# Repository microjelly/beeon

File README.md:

# beeon

## Overview
The classic device was created several years ago to fill a single need, preventing my work computer from auto locking due to inactivity. *Subverting security policy comes with a responsibility to ensure that you lock your computer (CTRL+ALT+DEL) everytime you walk away!*  

## classic notes
### flash bootloader to board
`avrdude -c USBasp -p attiny85 -U flash:w:beeon-classic-v1-micronucleus-2.04.hex:i -B 10`  
`avrdude -c USBasp -p attiny85 -U lfuse:w:0xe1:m -U hfuse:w:0xdd:m -U efuse:w:0xfe:m`  
### upload new firmware onto board
`micronucleus --run {firmware.hex}`
### clear out any existing firmware
`micronucleus --erase-only`
### upload firmware with random serial number
*first create random serial number file*  
`beeon-classic-sn -mk -mk-p=Z-ZZ > beeon-sn.txt`  
`beeon-classic-sn | micronucleus --run -`

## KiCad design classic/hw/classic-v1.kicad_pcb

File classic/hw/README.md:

[finished-product-image]: v1/img/classic-v1.jpg "BEEON - Classic; v1"
[pcb-top-image]: v1/img/classic-v1-top.png "BEEON - Classic; v1; pcb-top"
[pcb-bottom-image]: v1/img/classic-v1-bottom.png "BEEON - Classic; v1; pcb-bottom"

# classic hardware

## Overview
A brief overview of why we ave a classic version

## BOM
Some words aboutthe current bom
| Reference(s) | Package  | Description                    | Manufacturer      | Part Number        | Cost  |
| ------------ | -------: | ------------------------------ | ----------------- | -----------------: | ----: |
| SW1          |          | Switch                         | E-Switch          | *TL1014BF180QG     | $#.## |
| D1           | 1206     | LED                            | OSRAM Opto        | *LG N971-KN-1      | $#.## |
| J1           |          | 6 PIN 2.54mm (Optional Header) | Harwin            | M20-7820646        | $0.95 |
| J2           |          | USB                            | CNC-Tech          | 1001-011-01101     | $0.77 |
| R1           | 0805     | 47 Ohm Resistor                | Vishay/Dale       | CRCW080547R0FKEA   | $0.10 |
| R2           | 0805     | 1K5 Ohm Resistor               | Vishay/Dale       | CRCW08051K50FKEB   | $0.17 |
| R3           | 0805     | 68 Ohm Resistor                | Vishay/Dale       | CRCW080568R0FKEA   | $0.10 |
| R4           | 0805     | 68 Ohm Resistor                | Vishay/Dale       | CRCW080568R0FKEA   | $0.10 |
| U1           | SOIC-8   | ATtiny85 MCU                   | Atmel             | ATtiny85-20SU      | $1.13 |
| U2           | SOT-23-5 | 1 00mA 3.3 LDO                 | Texas Instruments | TPS79133DBVR       | $1.32 |
| C1           | 1206     | 10uF 10v Tantalum Capacitor    | AVX               | F931A106KAA        | $0.49 |
| C2           | 1206     | 0.1uF 10v MLCC Capacitor       | Vishay/Vitramon   | VJ1206Y104KXQPW1BC | $0.29 |
| C3           | 1206     | 0.01uF 10v MLCC Capacitor      | Vishay/Vitramon   | VJ1206Y103KXJCW1BC | $0.25 |
| C4           | 1206     | 1uF 16v Tantalum Capacitor     | AVX               | F931C105KAA        | $0.51 |

*obsolete part (need to find replacement)

## PCB
Some quick words about the pcb
| ![alt text][pcb-top-image] ![alt text][pcb-bottom-image]              | 
| --------------------------------------------------------------------: |
| [`Order from OSH Park`](https://oshpark.com/shared_projects/amtuUCdw) |

## Finished Product
Some quick words about the finished product
| ![alt text][finished-product-image] |
| :---------------------------------- |

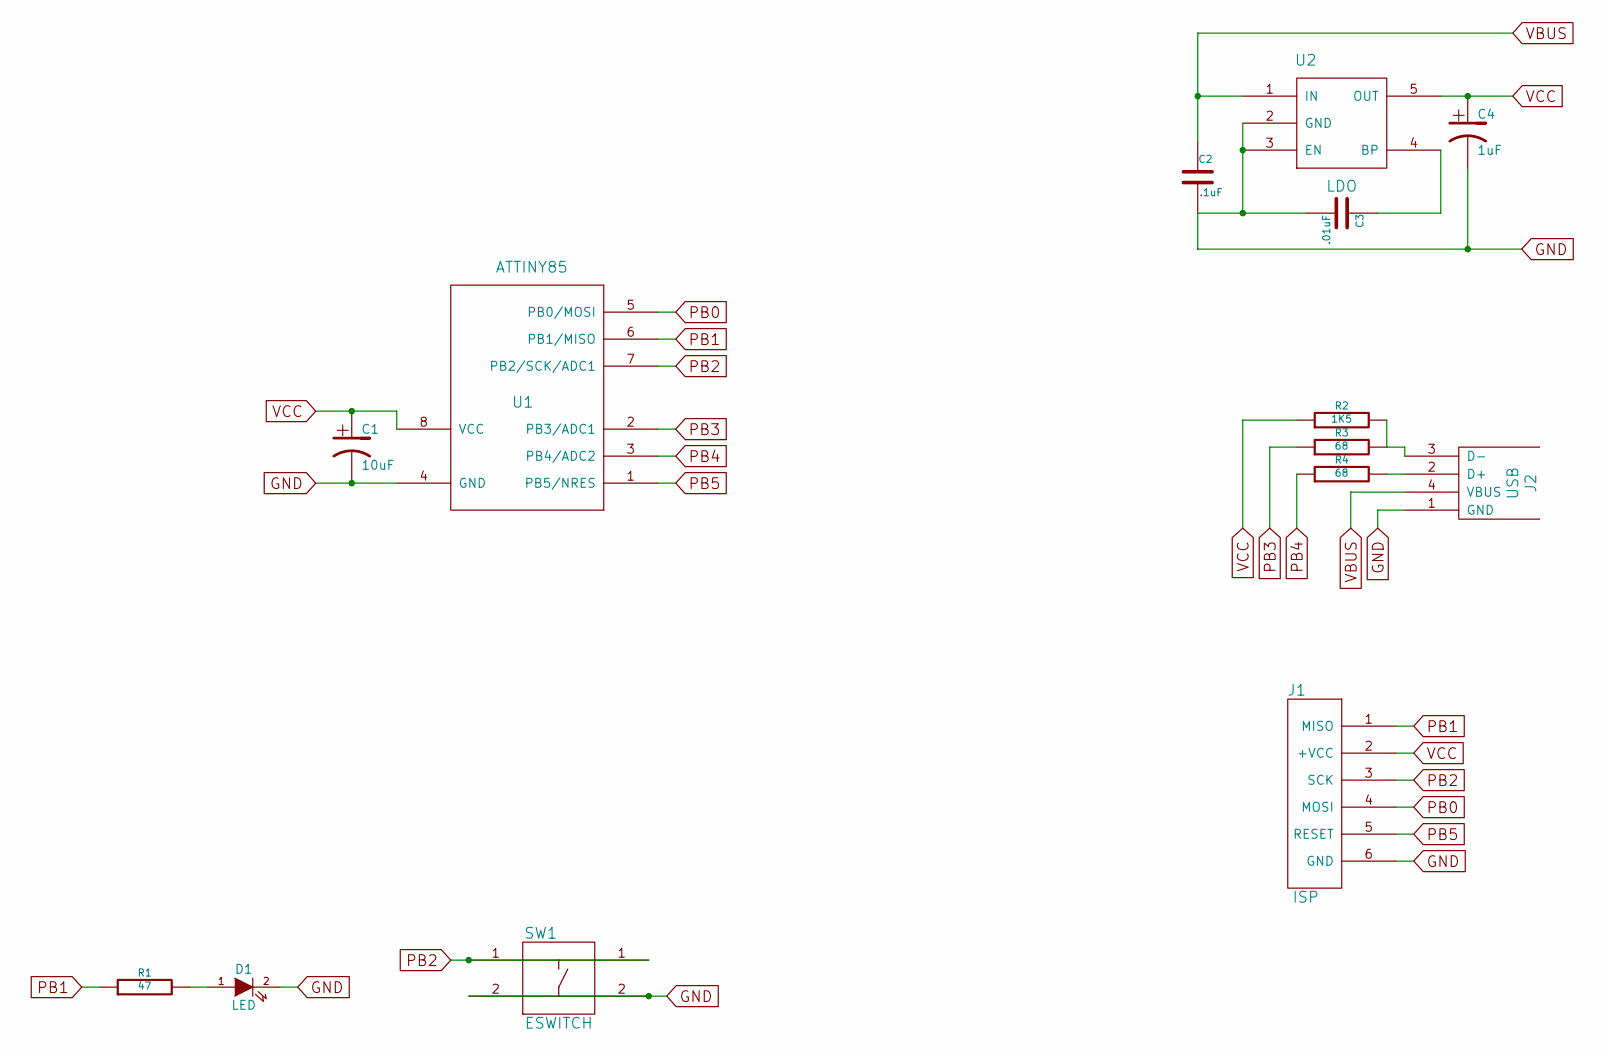
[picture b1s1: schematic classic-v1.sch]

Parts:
C1: 10uF
C2: .1uF
C3: .01uF
C4: 1uF
D1: LED
J1: ISP
J2: USB
R1: 47
R2: 1K5
R3, R4: 68
SW1: ESWITCH
U1: ATTINY85
U2: LDO

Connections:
GND: C1.2, C2.2, C3.2, C4.2, D1.2 (K), J1.6 (GND), J2.1 (GND), SW1.2, U1.4 (GND), U2.2 (GND), U2.3 (EN)
unnamed: J2.3 (D-), R2.2, R3.2
unnamed: J2.2 (D+), R4.2
unnamed: D1.1 (A), R1.2
unnamed: C3.1, U2.4 (BP)
PB0: J1.4 (MOSI), U1.5 (PB0/MOSI)
PB1: J1.1 (MISO), R1.1, U1.6 (PB1/MISO)
PB2: J1.3 (SCK), SW1.1, U1.7 (PB2/SCK/ADC1)
PB3: R3.1, U1.2 (PB3/ADC1)
PB4: R4.1, U1.3 (PB4/ADC2)
PB5: J1.5 (RESET), U1.1 (PB5/NRES)
VBUS: C2.1, J2.4 (VBUS), U2.1 (IN)
VCC: C1.1, C4.1, J1.2 (+VCC), R2.1, U1.8 (VCC), U2.5 (OUT)

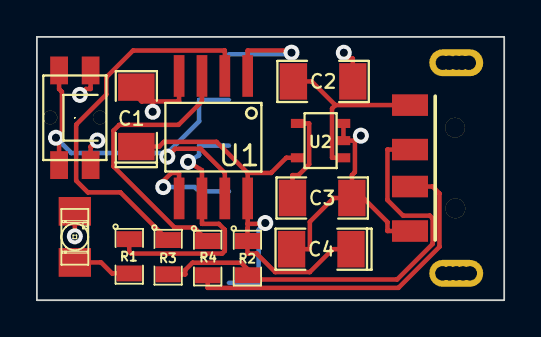
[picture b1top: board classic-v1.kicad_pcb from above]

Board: 2 copper layers, 26.0 x 14.6 mm, 14 parts (1 on the bottom side), 13 nets.

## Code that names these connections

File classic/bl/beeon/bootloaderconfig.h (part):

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 * 
 * Controller type: ATtiny 85 - 16.5 MHz
 * Configuration:   Default configuration
 *       USB D- :   PB3
 *       USB D+ :   PB4
 *       Entry  :   Always
 *       LED    :   None
 *       OSCCAL :   Stays at 16 MHz
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 *                      external jumper. 
 *                      Adds 34 bytes.
 *
 *       JUMPER_PIN     Pin the jumper is connected to. (e.g. PB0)
 *       JUMPER_PORT    Port out register for the jumper (e.g. PORTB)  
 *       JUMPER_DDR     Port data direction register for the jumper (e.g. DDRB)  
 *       JUMPER_INP     Port inout register for the jumper (e.g. PINB)  
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
#define ENTRYMODE ENTRY_JUMPER

#define JUMPER_PIN    PB2
#define JUMPER_PORT   PORTB 
#define JUMPER_DDR    DDRB 
#define JUMPER_INP    PINB 
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
#define LED_DDR     DDRB
#define LED_PORT    PORTB
#define LED_PIN     PB1

/*
 *  This is the implementation of the LED code. Change the configuration above unless you want to 
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
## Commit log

2020-08-11 notes
2020-08-11 classic
2020-08-13 x-cli
2020-08-13 whatChanged+
2020-08-14 images+
2020-08-14 movement
2020-08-15 readme
2020-08-15 small fixes

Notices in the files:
classic/bl/beeon/bootloaderconfig.h:
License: GNU GPL v2 (see License.txt
